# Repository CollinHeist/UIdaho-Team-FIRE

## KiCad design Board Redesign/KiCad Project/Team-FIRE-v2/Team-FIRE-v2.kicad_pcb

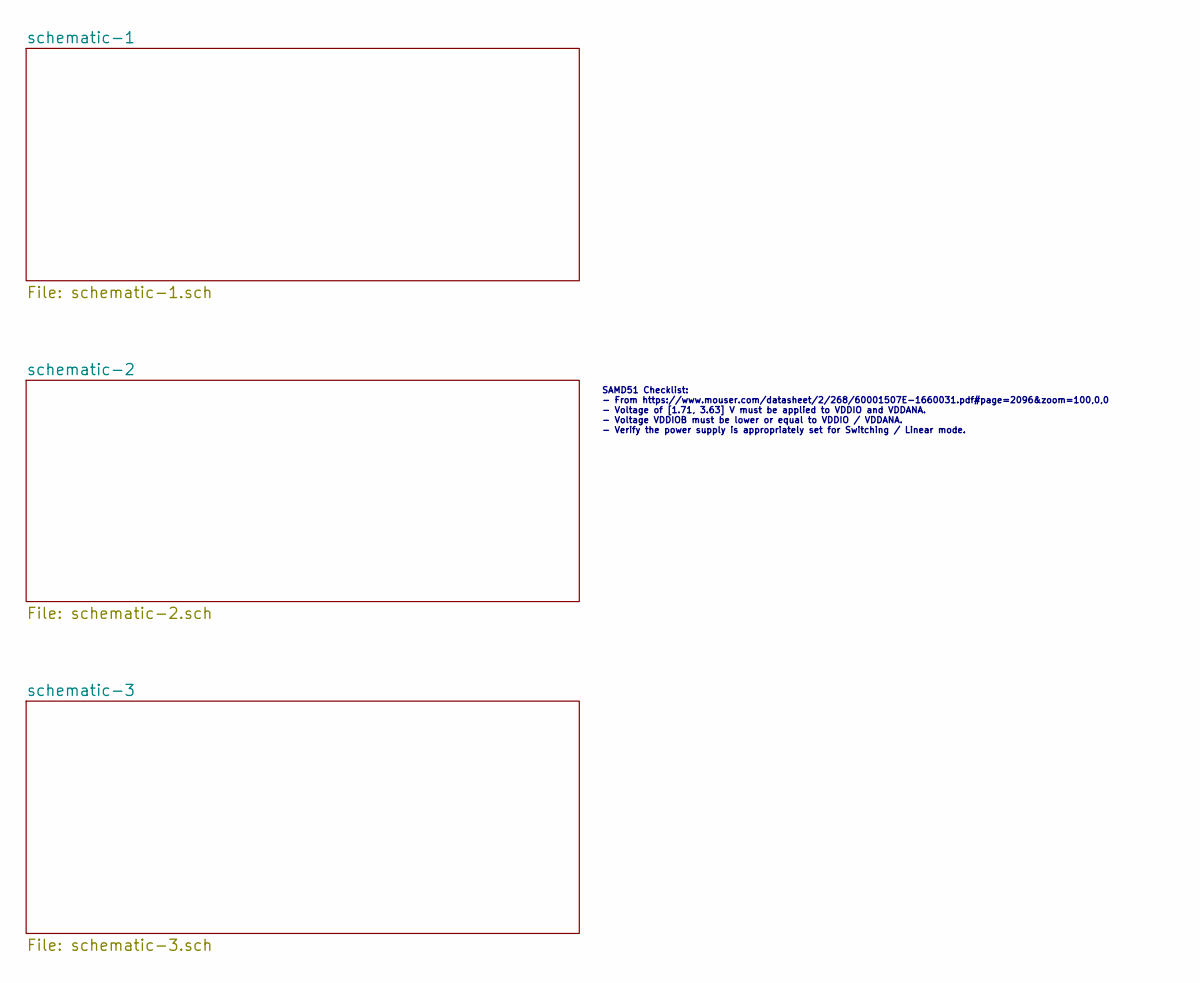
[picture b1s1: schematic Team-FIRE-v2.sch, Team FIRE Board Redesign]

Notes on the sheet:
SAMD51 Checklist: - From https://www.mouser.com/datasheet/2/268/60001507E-1660031.pdf#page=2096&zoom=100,0,0 - Voltage of [1.71, 3.63] V must be applied to VDDIO and VDDANA. - Voltage VDDIOB must be lower or equal to VDDIO / VDDANA. - Verify the power supply is appropriately set for Switching / Lin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

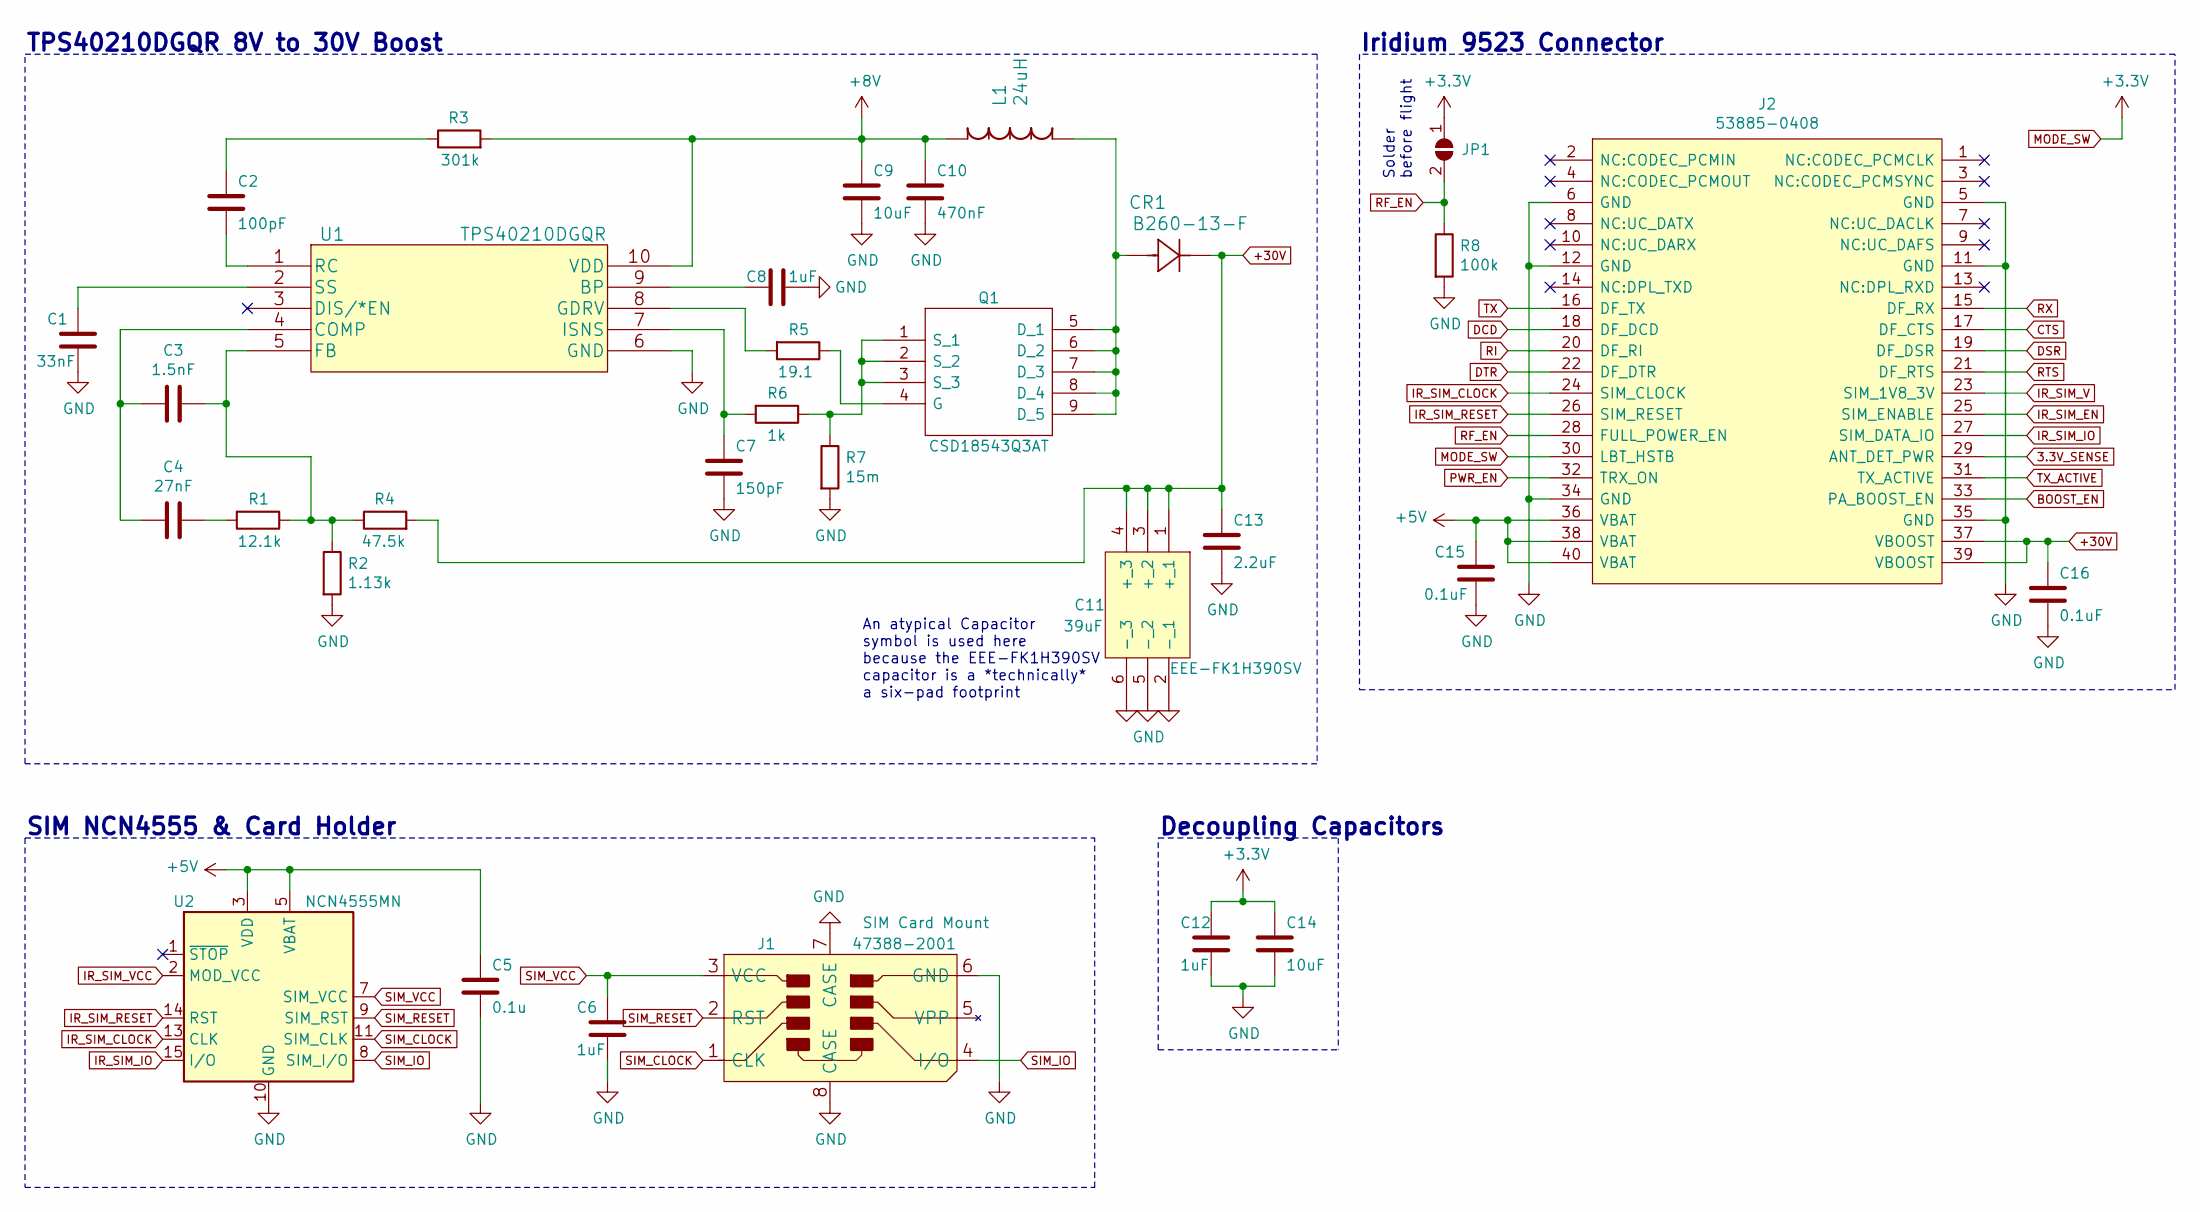
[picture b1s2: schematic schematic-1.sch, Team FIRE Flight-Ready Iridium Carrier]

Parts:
C1: 33nF; C_0603_1608Metric; Tolerance 5%; Voltage Rating 100 VDC; MPN C0603C333J1RECTU
C2: 100pF; C_0603_1608Metric; Tolerance 1%; Voltage Rating 50 VDC; MPN CBR06C101F5GAC
C3: 1.5nF; C_0603_1608Metric; Tolerance 5%; Voltage Rating 100 VDC; MPN C1608C0G2A152J080AE
C4: 27nF; C_0603_1608Metric; Tolerance 5%; Voltage Rating 25 VDC; MPN C0603C273J3RACTU
C5: 0.1u; C_0603_1608Metric; Tolerance 10%; Voltage Rating 50 VDC; MPN C0603C104K5RAC3121
C6, C12: 1uF; C_0603_1608Metric; Tolerance 10%; Voltage Rating 25 VDC; MPN TMK107BLD105KA-T
C7: 150pF; C_0603_1608Metric
C8: 1uF; C_0603_1608Metric
C9, C14: 10uF; C_0603_1608Metric; Tolerance 10%; Voltage Rating 25 VDC; MPN GRM188R61E106KA73D
C10: 470nF; C_0603_1608Metric; Tolerance 5%; Voltage Rating 16 VDC; MPN C0603C474J4RACAUTO
C11: 39uF; EEEFK1H390SV; Tolerance 20%; Voltage Rating 50 VDC; MPN EEE-FK1H390SV
C13: 2.2uF; C_0603_1608Metric; Voltage Rating 50 VDC; MPN GRM188R61H225KE11D
C15, C16: 0.1uF; C_0603_1608Metric; Tolerance 10%; Voltage Rating 50 VDC; MPN C0603C104K5RAC3121
CR1: B260-13-F; DIOM5336X250N; Voltage Rating 60 V; Current Rating 2 A; MPN B260-13-F
J1: 47388-2001; 473882001; Current Rating 500 mA; MPN 47388-2001
J2: 53885-0408; 538850408; Mouser Part Number 538-53885-0408
JP1: SolderJumper_2_Open; SolderJumper-2_P1.3mm_Open_Pad1.0x1.5mm
L1: 24uH; IHLP6767GZER220M11; Tolerance 20%; Current Rating 12 A; MPN IHLP6767GZER220M11
Q1: CSD18543Q3AT; MPN CSD18543Q3AT
R1: 12.1k; R_0603_1608Metric; Tolerance 0.1%; MPN ERJ-PB3B1212V
R2: 1.13k; R_0603_1608Metric; Tolerance 0.1%; MPN RQ73C1J1K13BTDF
R3: 301k; R_0603_1608Metric; Voltage Rating 75 V; Tolerance 1%; MPN CRCW0603301KFKEAHP
R4: 47.5k; R_0603_1608Metric; Tolerance 1%; Voltage Rating 75 V; MPN MCT06030C4752FP500
R5: 19.1; R_0603_1608Metric; Tolerance 1%; Voltage Rating 75 V; MPN ERJ-3EKF19R1V
R6: 1k; R_0603_1608Metric; Tolerance 0.1%; Voltage Rating 75 V; MPN MCT0603MD1001BP500
R7: 15m; R_0603_1608Metric; Tolerance 1%; MPN LVT06R0150FER
R8: 100k; R_0603_1608Metric; Tolerance 0.1%; Voltage Rating 75 V; MPN MCT06030E1003BP500
U1: TPS40210DGQR; MPN TPS40210DGQR
U2: NCN4555MN; QFN-16-1EP_3x3mm_P0.5mm_EP1.75x1.75mm; MPN NCN4555MNR2G

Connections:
3.3V_SENSE: J2.29 (ANT_DET_PWR); also elsewhere on the board
+5V: C5.1, C15.1, J2.36 (VBAT), J2.38 (VBAT), J2.40 (VBAT), U2.3 (VDD), U2.5 (VBAT); also elsewhere on the board
+8V: C9.1, C10.1, L1.2, R3.2, U1.10 (VDD)
+30V: C11.1 (+_1), C11.3 (+_2), C11.4 (+_3), C13.1, C16.1, CR1.1, J2.37 (VBOOST), J2.39 (VBOOST), R4.2
BOOST_EN: J2.33 (PA_BOOST_EN); also elsewhere on the board
CTS: J2.17 (DF_CTS); also elsewhere on the board
DCD: J2.18 (DF_DCD); also elsewhere on the board
DSR: J2.19 (DF_DSR); also elsewhere on the board
DTR: J2.22 (DF_DTR); also elsewhere on the board
GND: C1.2, C5.2, C6.2, C7.2, C8.1, C9.2, C10.2, C11.2 (-_1), C11.5 (-_2), C11.6 (-_3), C12.2, C13.2, C14.2, C15.2, C16.2, J1.6 (GND), J1.7 (CASE), J1.8 (CASE), J2.5 (GND), J2.6 (GND), J2.11 (GND), J2.12 (GND), J2.34 (GND), J2.35 (GND), R2.2, R7.2, R8.2, U1.6 (GND), U2.10 (GND), U2.17 (GND); also elsewhere on the board
IR_SIM_CLOCK: J2.24 (SIM_CLOCK), U2.13 (CLK)
IR_SIM_EN: J2.25 (SIM_ENABLE)
IR_SIM_IO: J2.27 (SIM_DATA_IO), U2.15 (I/O)
IR_SIM_RESET: J2.26 (SIM_RESET), U2.14 (RST)
IR_SIM_V: J2.23 (SIM_1V8_3V)
IR_SIM_VCC: U2.2 (MOD_VCC)
MODE_SW: C12.1, C14.1, J2.30 (LBT_HSTB), JP1.1 (A); also elsewhere on the board
unnamed: C1.1, U1.2 (SS)
unnamed: C2.1, R3.1
unnamed: C2.2, U1.1 (RC)
unnamed: C3.1, R1.1, R2.1, R4.1, U1.5 (FB)
unnamed: C3.2, C4.2, U1.4 (COMP)
unnamed: C4.1, R1.2
unnamed: C7.1, R6.2, U1.7 (ISNS)
unnamed: C8.2, U1.9 (BP)
unnamed: CR1.2, L1.1, Q1.5 (D_1), Q1.6 (D_2), Q1.7 (D_3), Q1.8 (D_4), Q1.9 (D_5)
unnamed: Q1.1 (S_1), Q1.2 (S_2), Q1.3 (S_3), R6.1, R7.1
unnamed: Q1.4 (G), R5.1
unnamed: R5.2, U1.8 (GDRV)
PWR_EN: J2.32 (TRX_ON); also elsewhere on the board
RF_EN: J2.28 (FULL_POWER_EN), JP1.2 (B), R8.1
RI: J2.20 (DF_RI); also elsewhere on the board
RTS: J2.21 (DF_RTS); also elsewhere on the board
RX: J2.15 (DF_RX); also elsewhere on the board
SIM_CLOCK: J1.1 (CLK), U2.11 (SIM_CLK)
SIM_IO: J1.4 (I/O), U2.8 (SIM_I/O)
SIM_RESET: J1.2 (RST), U2.9 (SIM_RST)
SIM_VCC: C6.1, J1.3 (VCC), U2.7 (SIM_VCC)
TX: J2.16 (DF_TX); also elsewhere on the board
TX_ACTIVE: J2.31 (TX_ACTIVE); also elsewhere on the board

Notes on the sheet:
Iridium 9523 Connector
SIM NCN4555 & Card Holder
Solder before flight
Decoupling Capacitors
TPS40210DGQR 8V to 30V Boost
An atypical Capacitor symbol is used here because the EEE-FK1H390SV capacitor is a *technically* a six-pad footprint

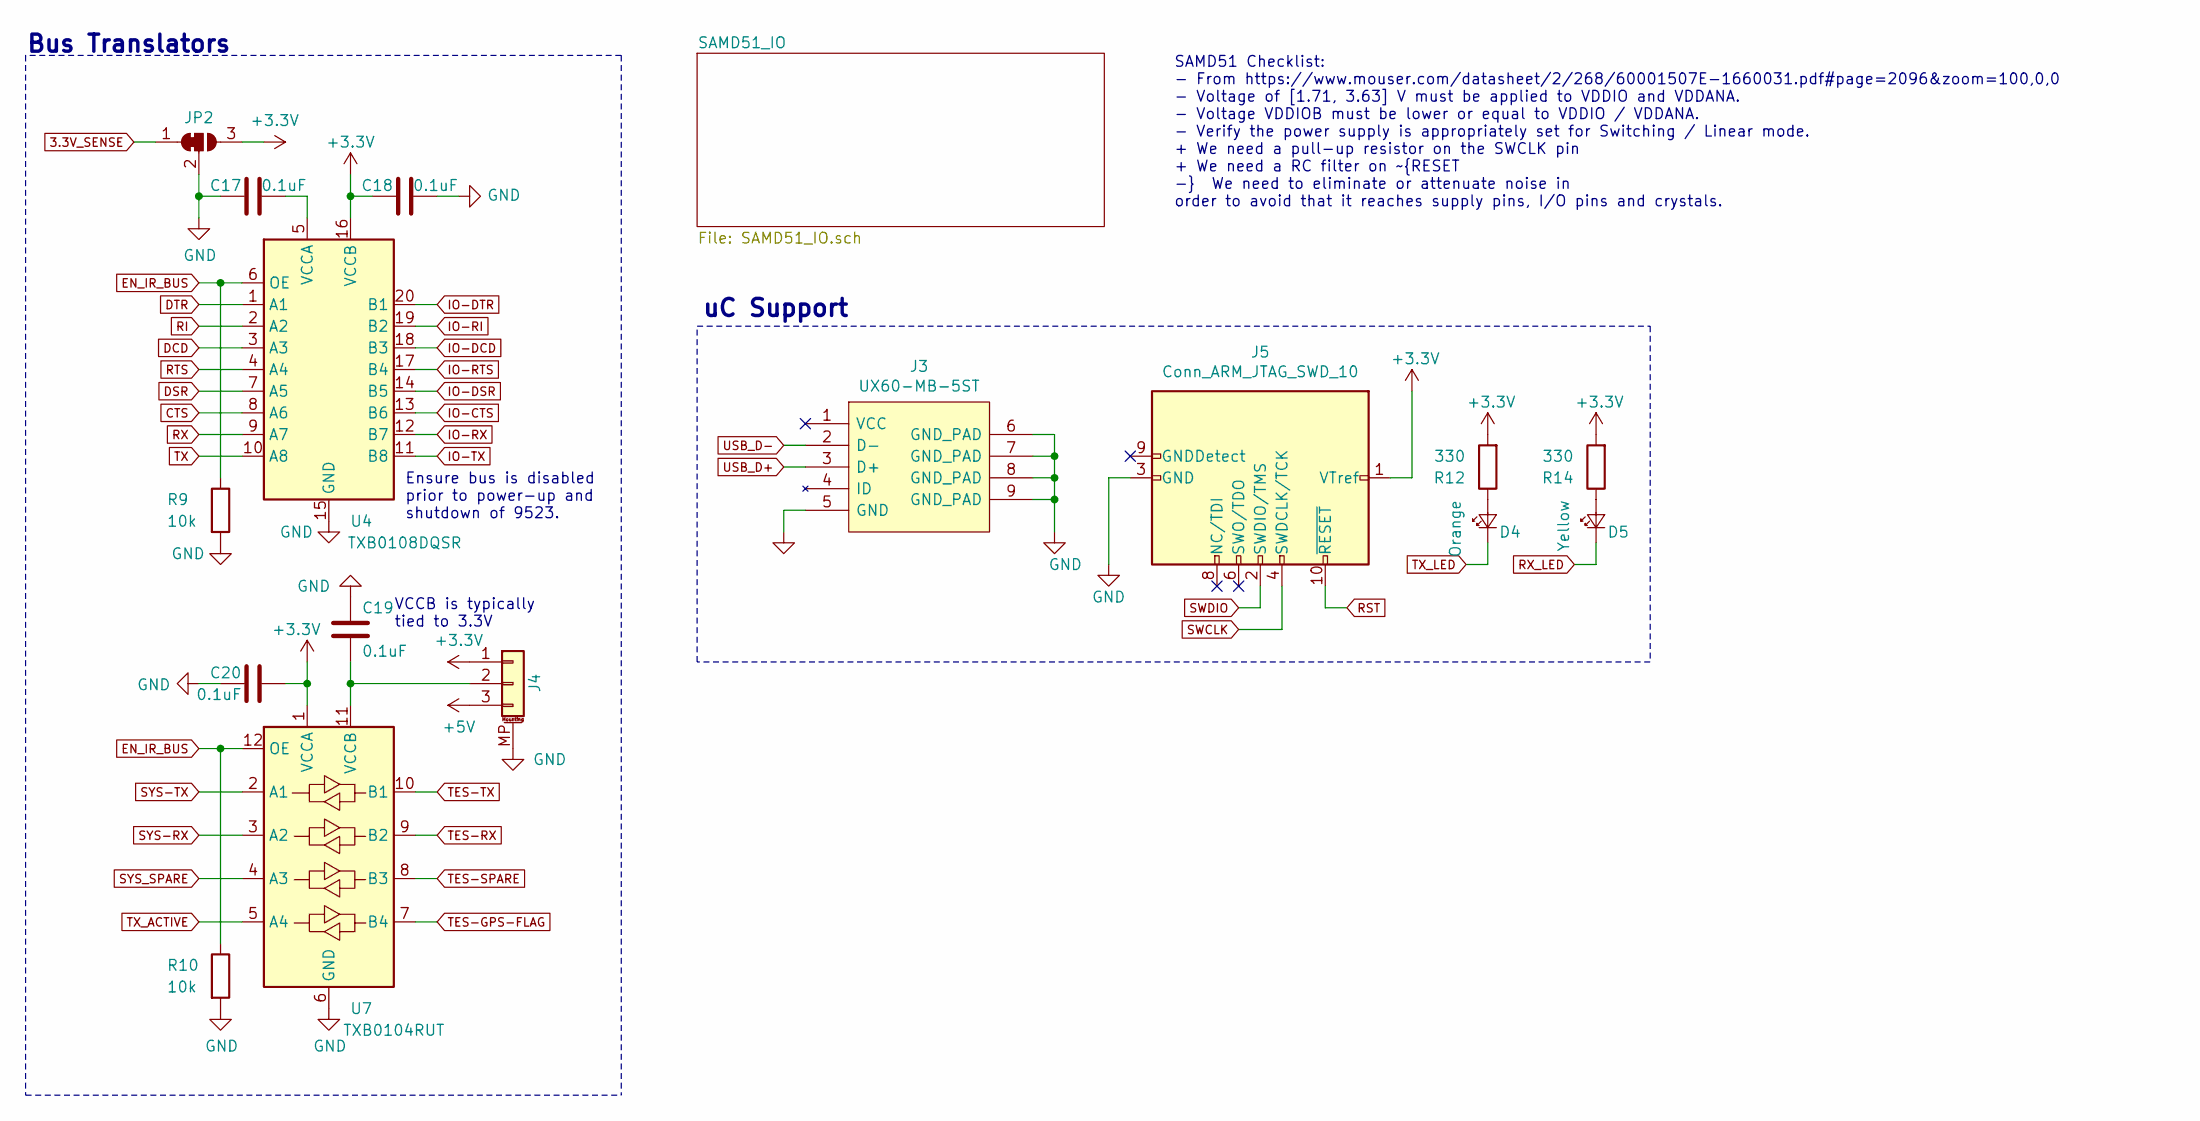
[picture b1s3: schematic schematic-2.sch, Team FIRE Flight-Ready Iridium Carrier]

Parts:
C17, C18, C19, C20: 0.1uF; C_0603_1608Metric; Tolerance 10%; Voltage Rating 50 VDC; MPN C0603C104K5RAC3121
D4: Orange; LED_0603_1608Metric; MPN KO DELLS1.22-KHLI-24
D5: Yellow; LED_0603_1608Metric; MPN KY DELLS1.22-KGLH-26
J3: UX60-MB-5ST; HIROSE-UX60-MB-5ST; MPN UX60-MB-5ST
J4: Conn_01x03; JST_S3B-PH-SM4-TB(LF)(SN); Voltage Rating 100 V; Current Rating 2 A; MPN S3B-PH-SM4-TB(LF)(SN)
J5: Conn_ARM_JTAG_SWD_10; PinHeader_2x05_P1.27mm_Vertical_SMD; Current Rating 3.4 A per contact; MPN FTSH-105-01-L-DV-K-TR
JP2: SolderJumper_3_Bridged12; SolderJumper-3_P1.3mm_Bridged2Bar12_RoundedPad1.0x1.5mm
R9, R10: 10k; R_0603_1608Metric; Tolerance 0.1%; Voltage Rating 75 V; MPN MCT06030E1002BP100
R12, R14: 330; R_0603_1608Metric; Tolerance 1%; Voltage Rating 75 V; MPN SR0603FR-7T330RL
U4: TXB0108DQSR; USON-20_2x4mm_P0.4mm; Voltage Rating 1.2/1.65 V to 5.5 V
U7: TXB0104RUT; Texas_R_PUQFN-N12; Voltage Rating 1.2/1.65 V to 5.5 V; MPN TXB0104RUTR

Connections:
3.3V_SENSE: JP2.1 (A); also elsewhere on the board
+5V: J4.3; also elsewhere on the board
CTS: U4.8 (A6); also elsewhere on the board
DCD: U4.3 (A3); also elsewhere on the board
DSR: U4.7 (A5); also elsewhere on the board
DTR: U4.1 (A1); also elsewhere on the board
EN_IR_BUS: R9.1, R10.1, U4.6 (OE), U7.12 (OE); also elsewhere on the board
GND: C17.1, C18.2, C19.1, C20.1, J3.5 (GND), J3.6 (GND_PAD), J3.7 (GND_PAD), J3.8 (GND_PAD), J3.9 (GND_PAD), J4.MP (MountPin), J5.3 (GND), J5.5 (GND), JP2.2 (C), R9.2, R10.2, U4.15 (GND), U7.6 (GND); also elsewhere on the board
IO-CTS: U4.13 (B6); also elsewhere on the board
IO-DCD: U4.18 (B3); also elsewhere on the board
IO-DSR: U4.14 (B5); also elsewhere on the board
IO-DTR: U4.20 (B1); also elsewhere on the board
IO-RI: U4.19 (B2); also elsewhere on the board
IO-RTS: U4.17 (B4); also elsewhere on the board
IO-RX: U4.12 (B7); also elsewhere on the board
IO-TX: U4.11 (B8); also elsewhere on the board
MODE_SW: C18.1, C20.2, J4.1, J5.1 (VTref), JP2.3 (B), R12.2, R14.2, U4.16 (VCCB), U7.1 (VCCA); also elsewhere on the board
unnamed: C17.2, U4.5 (VCCA)
unnamed: C19.2, J4.2, U7.11 (VCCB)
unnamed: D4.2 (A), R12.1
unnamed: D5.2 (A), R14.1
RI: U4.2 (A2); also elsewhere on the board
RST: J5.10 (~RESET~); also elsewhere on the board
RTS: U4.4 (A4); also elsewhere on the board
RX: U4.9 (A7); also elsewhere on the board
RX_LED: D5.1 (K); also elsewhere on the board
SWCLK: J5.4 (SWDCLK/TCK); also elsewhere on the board
SWDIO: J5.2 (SWDIO/TMS); also elsewhere on the board
SYS-RX: U7.3 (A2); also elsewhere on the board
SYS-TX: U7.2 (A1); also elsewhere on the board
SYS_SPARE: U7.4 (A3)
TES-GPS-FLAG: U7.7 (B4); also elsewhere on the board
TES-RX: U7.9 (B2); also elsewhere on the board
TES-SPARE: U7.8 (B3)
TES-TX: U7.10 (B1); also elsewhere on the board
TX: U4.10 (A8); also elsewhere on the board
TX_ACTIVE: U7.5 (A4); also elsewhere on the board
TX_LED: D4.1 (K); also elsewhere on the board
USB_D+: J3.3 (D+); also elsewhere on the board
USB_D-: J3.2 (D-); also elsewhere on the board

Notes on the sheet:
uC Support
SAMD51 Checklist: - From https://www.mouser.com/datasheet/2/268/60001507E-1660031.pdf#page=2096&zoom=100,0,0 - Voltage of [1.71, 3.63] V must be applied to VDDIO and VDDANA. - Voltage VDDIOB must be lower or equal to VDDIO / VDDANA. - Verify the power supply is appropriately set for Switching / Lin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
VCCB is typically tied to 3.3V
Ensure bus is disabled prior to power-up and shutdown of 9523.
Bus Translators

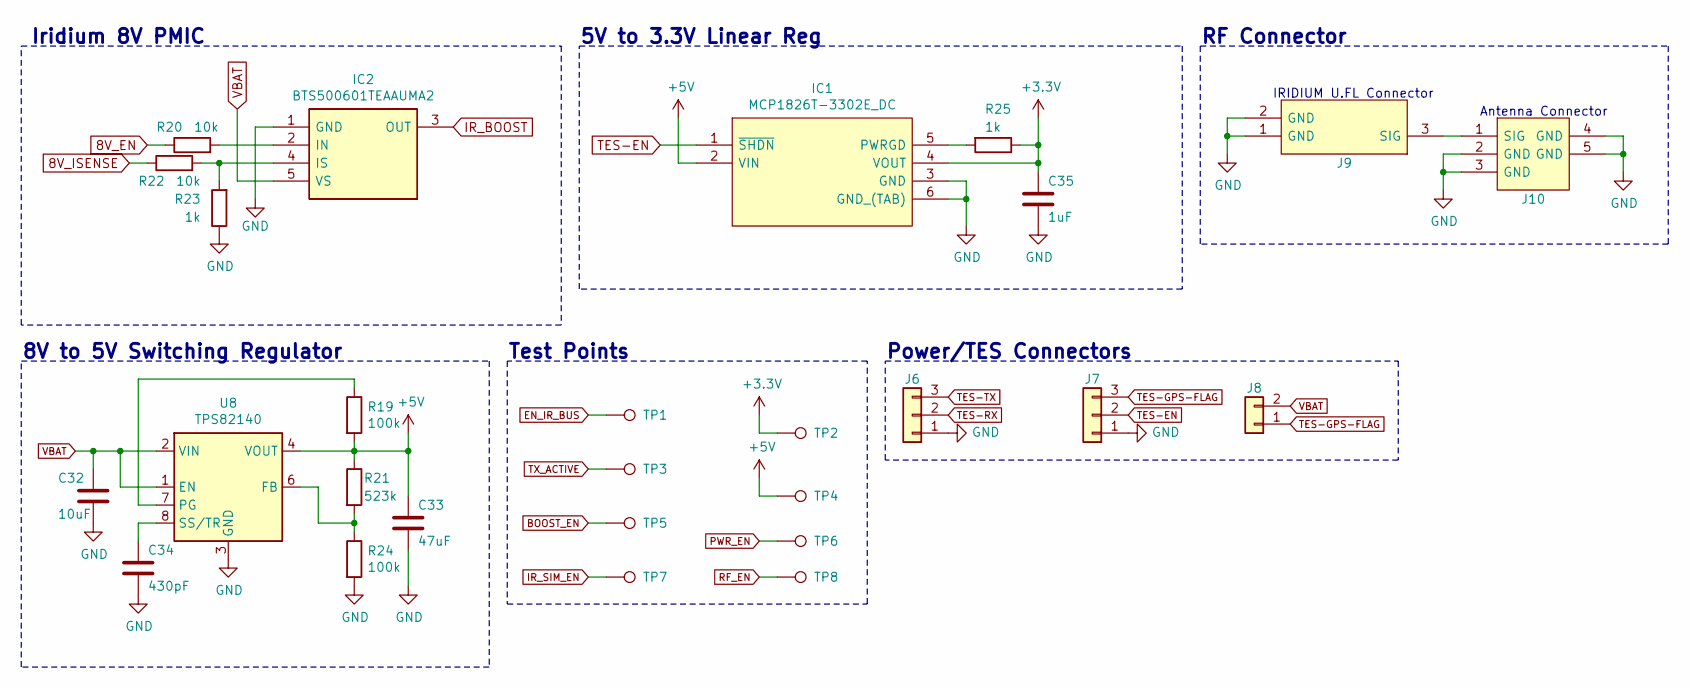
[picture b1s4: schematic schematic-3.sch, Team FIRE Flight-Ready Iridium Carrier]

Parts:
C32: 10uF; C_0603_1608Metric; Tolerance 10%; Voltage Rating 25 VDC; MPN GRM188R61E106KA73D
C33: 47uF; C_0805_2012Metric; Tolerance 20%; Voltage Rating 6.3 VDC; MPN JMK107BBJ476MA-RE
C34: 430pF; C_0603_1608Metric; Tolerance 5%; Voltage Rating 50 VDC; MPN 06035C431JAT2A
C35: 1uF; C_0603_1608Metric; Tolerance 10%; Voltage Rating 25 VDC; MPN TMK107BLD105KA-T
IC1: MCP1826T-3302E_DC; SOT127P706X180-6N; MPN MCP1826T-3302E/DC
IC2: BTS500601TEAAUMA2; MPN BTS500601TEAAUMA2
J6, J7: Conn_01x03; JST_SH_SM03B-SRSS-TB_1x03-1MP_P1.00mm_Horizontal; MPN SM03B-SRSS-TB(LF)(SN)
J8: Conn_01x02; 43650-0200; MPN 43650-0200
J9: U.FL-R-SMT_10_; UFLRSMT10; MPN U.FL-R-SMT(10)
J10: PCB.MMCX.F.ST.SMT.JACK.HT; PCBMMCXFSTSMTJACKHT; MPN PCB.MMCX.F.ST.SMT.JACK.HT
R19, R24: 100k; R_0603_1608Metric; Tolerance 0.1%; Voltage Rating 75 V; MPN MCT06030E1003BP500
R20, R22: 10k; R_0603_1608Metric; Tolerance 0.1%; Voltage Rating 75 V; MPN MCT06030E1002BP100
R21: 523k; R_0805_2012Metric; Tolerance 0.5%; Voltage Ratign 150 V; MPN ERJ-PB6D5233V
R23, R25: 1k; R_0603_1608Metric; Tolerance 0.1%; Voltage Rating 75 V; MPN MCT0603MD1001BP500
TP1, TP2, TP3, TP4, TP5, TP6, TP7, TP8: TestPoint; TestPoint_Pad_D1.0mm
U8: TPS82140; Texas_SIL0008D_MicroSiP-8-1EP_2.8x3mm_P0.65mm_EP1.1x1.9mm_T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; Voltage Rating 3 to 17 V; Current Rating 2 A; MPN TPS82140SILR

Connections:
8V_EN: R20.1; also elsewhere on the board
8V_ISENSE: R22.1; also elsewhere on the board
+5V: C33.1, IC1.2 (VIN), R19.2, R21.1, TP4.1, U8.4 (VOUT), U8.5 (VOUT); also elsewhere on the board
GND: C32.2, C33.2, C34.2, C35.2, IC1.3 (GND), IC1.6 (GND_(TAB)), IC2.1 (GND), J6.1, J7.1, J9.1 (GND), J9.2 (GND), J10.2 (GND), J10.3 (GND), J10.4 (GND), J10.5 (GND), R23.1, R24.2, U8.3 (GND), U8.9 (GND); also elsewhere on the board
IR_BOOST: IC2.3 (OUT)
MODE_SW: C35.1, IC1.4 (VOUT), R25.1, TP2.1; also elsewhere on the board
unnamed: C34.1, U8.8 (SS/TR)
unnamed: IC1.5 (PWRGD), R25.2
unnamed: IC2.2 (IN), R20.2
unnamed: IC2.4 (IS), R22.2, R23.2
unnamed: J9.3 (SIG), J10.1 (SIG)
unnamed: R19.1, U8.7 (PG)
unnamed: R21.2, R24.1, U8.6 (FB)
TES-EN: IC1.1 (~SHDN), J7.2
TES-GPS-FLAG: J7.3, J8.1; also elsewhere on the board
TES-RX: J6.2; also elsewhere on the board
TES-TX: J6.3; also elsewhere on the board
VBAT: C32.1, IC2.5 (VS), J8.2, U8.1 (EN), U8.2 (VIN)

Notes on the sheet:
RF Connector
Test Points
Iridium 8V PMIC
5V to 3.3V Linear Reg
IRIDIUM U.FL Connector
Antenna Connector
8V to 5V Switching Regulator
Power/TES Connectors

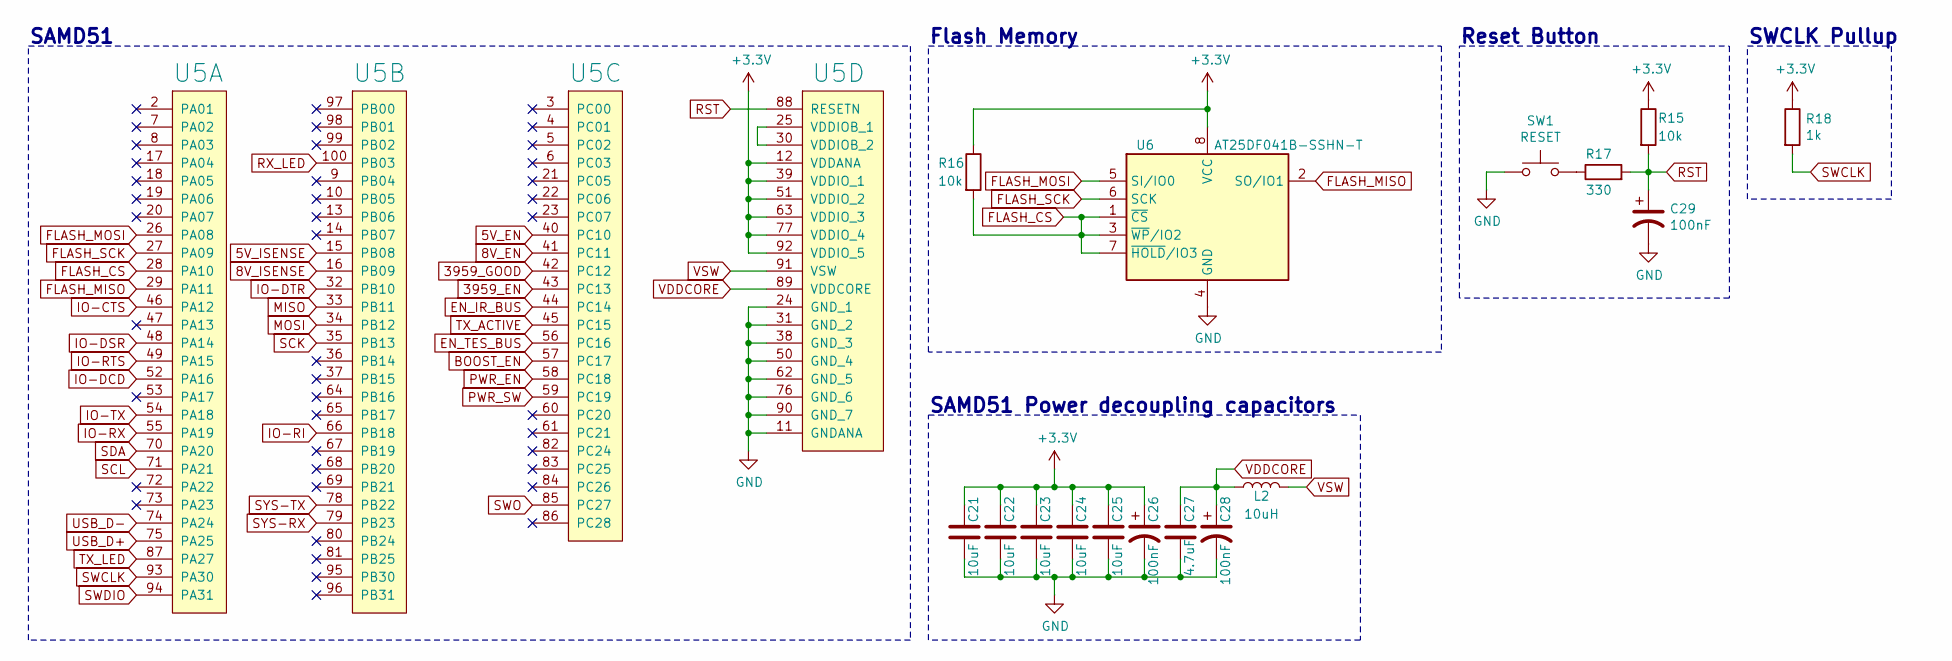
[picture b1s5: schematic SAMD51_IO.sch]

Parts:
C21, C22, C23, C24, C25: 10uF; C_0603_1608Metric; Tolerance 10%; Voltage Rating 25 VDC; MPN GRM188R61E106KA73D
C26, C28, C29: 100nF; C_0603_1608Metric; Tolerance 10%; Voltage Rating 50 VDC; MPN C0603X104K5RAC3316
C27: 4.7uF; C_0603_1608Metric; Tolerance 10%; Voltage Rating 35 VDC; MPN GMK107BBJ475KA-T
L2: 10uH; L_0603_1608Metric; Tolerance 20%; Current Rating 0.25 A; MPN KLZ1608MHR100WTD25
R15, R16: 10k; R_0603_1608Metric; Tolerance 0.1%; Voltage Rating 75 V; MPN MCT06030E1002BP100
R17: 330; R_0603_1608Metric; Tolerance 1%; Voltage Rating 75 V; MPN SR0603FR-7T330RL
R18: 1k; R_0603_1608Metric; Tolerance 0.1%; Voltage Rating 75 V; MPN MCT0603MD1001BP500
SW1: RESET; SW_SPST_EVQQ2; Voltage Rating 15 VDC, 250 VAC; Current Rating 20 mA; MPN EVQ-Q2Y03W
U5: SAMD51; TQFP-100_14x14mm_P0.5mm; MPN ATSAMD51N20A-AUT
U6: AT25DF041B-SSHN-T; SOIC-8_3.9x4.9mm_P1.27mm; Voltage Rating 1.65 - 3.6 V; MPN AT25DF041B-SSHN-T

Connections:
5V_EN: U5.40 (PC10)
5V_ISENSE: U5.15 (PB08)
8V_EN: U5.41 (PC11); also elsewhere on the board
8V_ISENSE: U5.16 (PB09); also elsewhere on the board
3959_EN: U5.43 (PC13)
3959_GOOD: U5.42 (PC12)
BOOST_EN: U5.57 (PC17); also elsewhere on the board
EN_IR_BUS: U5.44 (PC14); also elsewhere on the board
EN_TES_BUS: U5.56 (PC16)
FLASH_CS: R16.2, U5.28 (PA10), U6.1 (~CS), U6.3 (~WP~/IO2), U6.7 (~HOLD~/IO3)
FLASH_MISO: U5.29 (PA11), U6.2 (SO/IO1)
FLASH_MOSI: U5.26 (PA08), U6.5 (SI/IO0)
FLASH_SCK: U5.27 (PA09), U6.6 (SCK)
GND: C21.2, C22.2, C23.2, C24.2, C25.2, C26.2, C27.2, C28.2, C29.2, SW1.1, U5.11 (GNDANA), U5.24 (GND_1), U5.31 (GND_2), U5.38 (GND_3), U5.50 (GND_4), U5.62 (GND_5), U5.76 (GND_6), U5.90 (GND_7), U6.4 (GND); also elsewhere on the board
IO-CTS: U5.46 (PA12); also elsewhere on the board
IO-DCD: U5.52 (PA16); also elsewhere on the board
IO-DSR: U5.48 (PA14); also elsewhere on the board
IO-DTR: U5.32 (PB10); also elsewhere on the board
IO-RI: U5.66 (PB18); also elsewhere on the board
IO-RTS: U5.49 (PA15); also elsewhere on the board
IO-RX: U5.55 (PA19); also elsewhere on the board
IO-TX: U5.54 (PA18); also elsewhere on the board
MISO: U5.33 (PB11)
MODE_SW: C21.1, C22.1, C23.1, C24.1, C25.1, C26.1, R15.1, R16.1, R18.1, U5.12 (VDDANA), U5.39 (VDDIO_1), U5.51 (VDDIO_2), U5.63 (VDDIO_3), U5.77 (VDDIO_4), U5.92 (VDDIO_5), U6.8 (VCC); also elsewhere on the board
MOSI: U5.34 (PB12)
unnamed 78: R17.1, SW1.2; also elsewhere on the board
unnamed: U5.25 (VDDIOB_1), U5.30 (VDDIOB_2)
PWR_EN: U5.58 (PC18); also elsewhere on the board
PWR_SW: U5.59 (PC19)
RST: C29.1, R15.2, R17.2, U5.88 (RESETN); also elsewhere on the board
RX_LED: U5.100 (PB03); also elsewhere on the board
SCK: U5.35 (PB13)
SCL: U5.71 (PA21)
SDA: U5.70 (PA20)
SWCLK: R18.2, U5.93 (PA30); also elsewhere on the board
SWDIO: U5.94 (PA31); also elsewhere on the board
SWO: U5.85 (PC27)
SYS-RX: U5.79 (PB23); also elsewhere on the board
SYS-TX: U5.78 (PB22); also elsewhere on the board
TX_ACTIVE: U5.45 (PC15); also elsewhere on the board
TX_LED: U5.87 (PA27); also elsewhere on the board
USB_D+: U5.75 (PA25); also elsewhere on the board
USB_D-: U5.74 (PA24); also elsewhere on the board
VDDCORE: C27.1, C28.1, L2.1, U5.89 (VDDCORE)
VSW: L2.2, U5.91 (VSW)

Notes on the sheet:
Flash Memory
Reset Button
SWCLK Pullup
SAMD51 Power decoupling capacitors
SAMD51

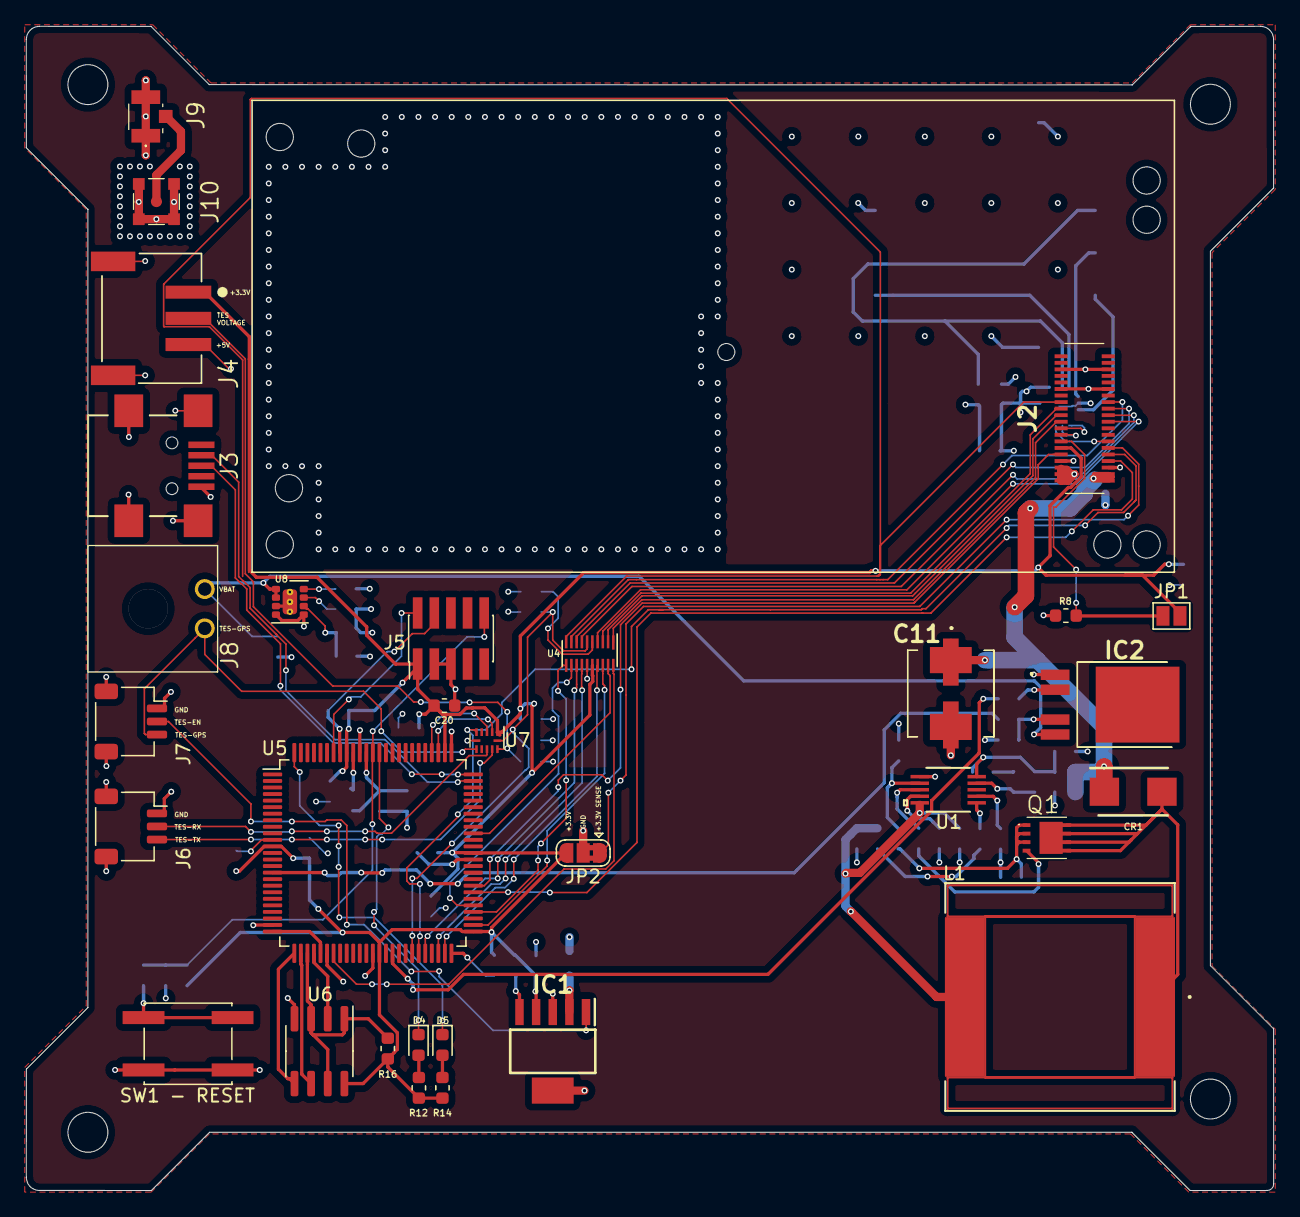
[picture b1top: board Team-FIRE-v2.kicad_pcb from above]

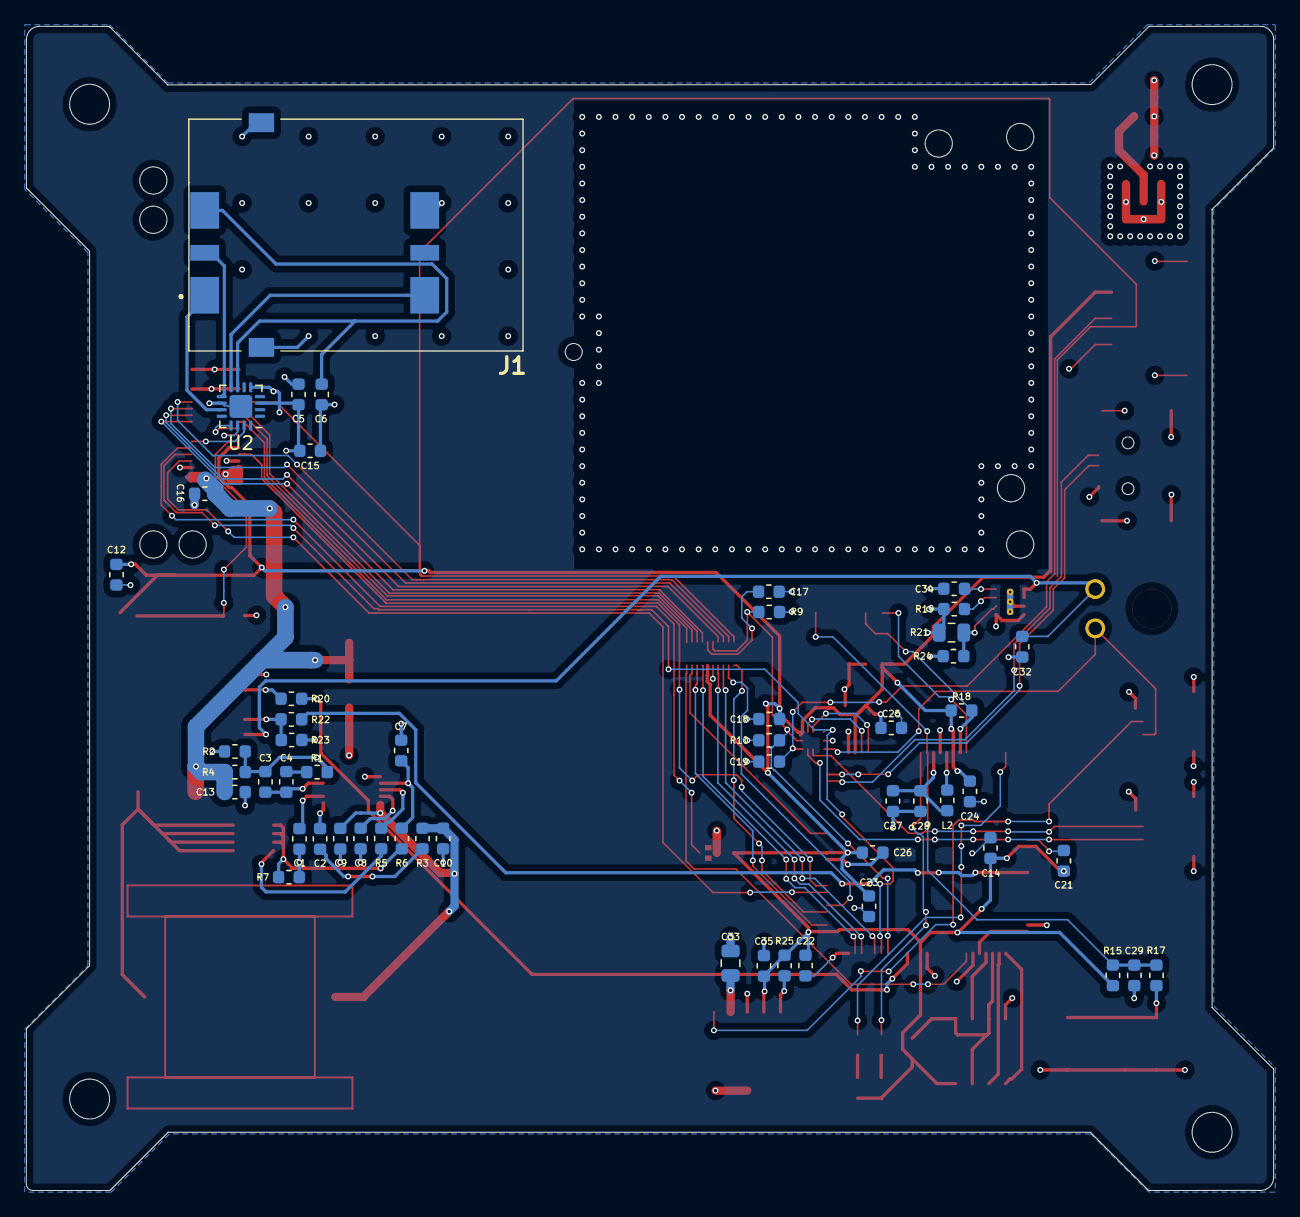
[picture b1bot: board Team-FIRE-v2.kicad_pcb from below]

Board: 4 copper layers, 95.2 x 88.9 mm, 84 parts (53 on the bottom side), 81 nets.

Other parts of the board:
SW1 - RESET: RESET; SW_SPST_EVQQ2

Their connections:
GND: SW1 - RESET.1; also elsewhere on the board
unnamed 78: SW1 - RESET.2; also elsewhere on the board
